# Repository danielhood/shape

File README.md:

# shape
Analog audio shaping toys. Line level moudles as opposed to eurorack i/o, but operating on +12/-12 power rails. The panels are built to be housed in 3U eurorack cases for the power supplies, but use 1/4" audio connectors. 

## 	saturation
A tape saturation/distortion unit based on: http://zadvitsky.com/index.php/studio-devices/tape-saturation-compressor.html
This was built and wired in as a bypassable 2nd stage to the var_state_eq module. A future revision would likely have a blend pot to add in the saturated signal from the EQ'd signal (need to review phase issues).

## var_state_eq
A State Variable Filter 2 Band EQ moudle based on the CALREC PQ1549 (only the HMF and LMF circuits), adapted from: https://www.gyraf.dk/gy_pd/calreq/calrec.htm

## compression
A compressor. WIP. Will be based on a few existing things; other than op-amps, will be discrete components (no THAT chips, etc.).

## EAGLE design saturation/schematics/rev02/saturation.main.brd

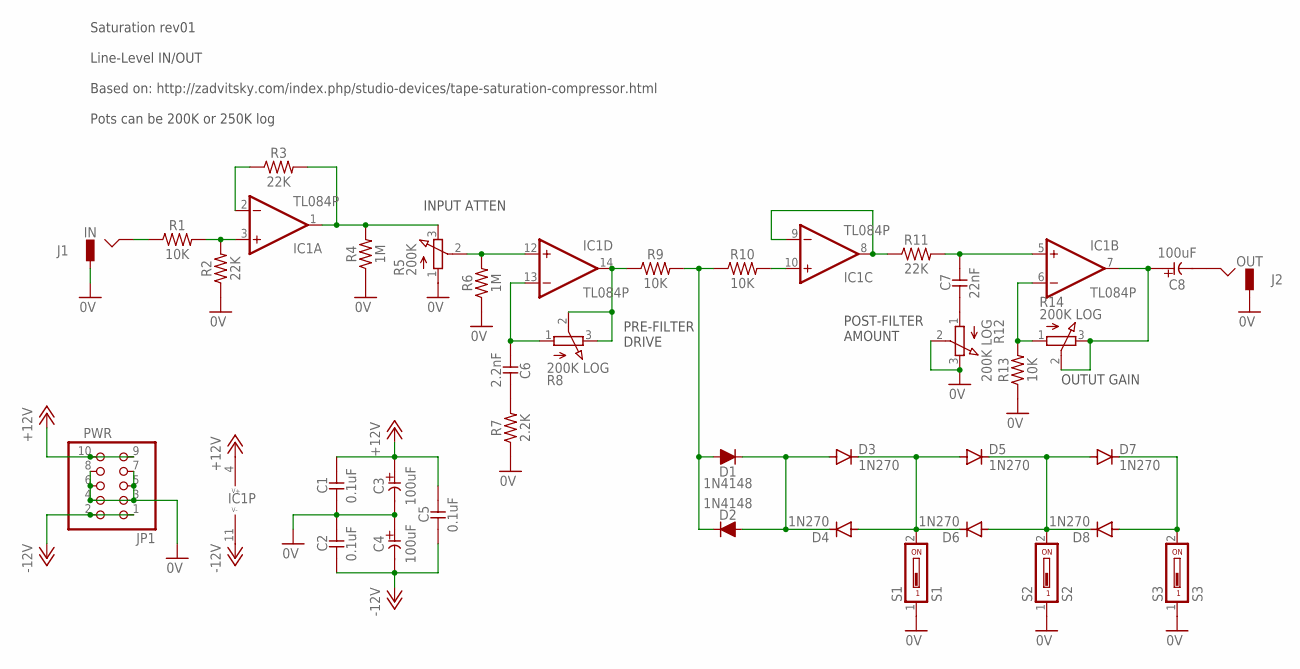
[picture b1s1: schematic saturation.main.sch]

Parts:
C1, C2, C5: 0.1uF; C025-024X044
C3, C4, C8: 100uF; E5-8,5
C6: 2.2nF; C025-024X044
C7: 22nF; C025-024X044
D1, D2: 1N4148; DO34-5
D3, D4, D5, D6, D7, D8: 1N270; DO07
IC1: TL084P; DIL14
J1: IN; JACK-M
J2: OUT; JACK-M
JP1: PWR; 2X05
R1, R9, R10, R13: 10K; 0207/7
R2, R3, R11: 22K; 0207/7
R4, R6: 1M; 0207/7
R5: 200K; 3RP/1610N
R7: 2.2K; 0207/7
R8, R12, R14: 200K LOG; 3RP/1610N
S1: S1; DS-01
S2: S2; DS-01
S3: S3; DS-01

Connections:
0V: C1.2, C2.1, C3.-, C4.+, J1.GND, J2.GND, JP1.3, JP1.4, JP1.5, JP1.6, JP1.7, JP1.8, R2.1, R4.1, R5.1 (A), R6.1, R7.1, R12.2 (S), R12.3 (E), R13.1, S1.1, S2.1, S3.1
+12V: C1.1, C3.+, C5.1, IC1.4 (V+), JP1.9, JP1.10
-12V: C2.2, C4.-, C5.2, IC1.11 (V-), JP1.1, JP1.2
unnamed: D1.A, D2.C, R9.2, R10.1
unnamed: C7.2, R12.1 (A)
unnamed: D1.C, D2.A, D3.A, D4.C
unnamed: D3.C, D4.A, D5.A, D6.C, S1.2
unnamed: IC1.10 (+IN), R10.2
unnamed: D5.C, D6.A, D7.A, D8.C, S2.2
unnamed: IC1.8 (OUT), IC1.9 (-IN), R11.1
unnamed: D7.C, D8.A, S3.2
unnamed: C7.1, IC1.5 (+IN), R11.2
unnamed: IC1.6 (-IN), R13.2, R14.1 (A)
unnamed: C8.+, IC1.7 (OUT), R14.2 (S), R14.3 (E)
unnamed: C8.-, J2.HOT
unnamed: IC1.14 (OUT), R8.2 (S), R8.3 (E), R9.1
unnamed: C6.1, R7.2
unnamed: J1.HOT, R1.1
unnamed: IC1.3 (+IN), R1.2, R2.2
unnamed: IC1.2 (-IN), R3.1
unnamed: IC1.1 (OUT), R3.2, R4.2, R5.3 (E)
unnamed: C6.2, IC1.13 (-IN), R8.1 (A)
unnamed: IC1.12 (+IN), R5.2 (S), R6.2

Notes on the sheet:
Saturation rev01 Line-Level IN/OUT Based on: http://zadvitsky.com/index.php/studio-devices/tape-saturation-compressor.html Pots can be 200K or 250K log
PRE-FILTER DRIVE
POST-FILTER AMOUNT
INPUT ATTEN
OUTUT GAIN

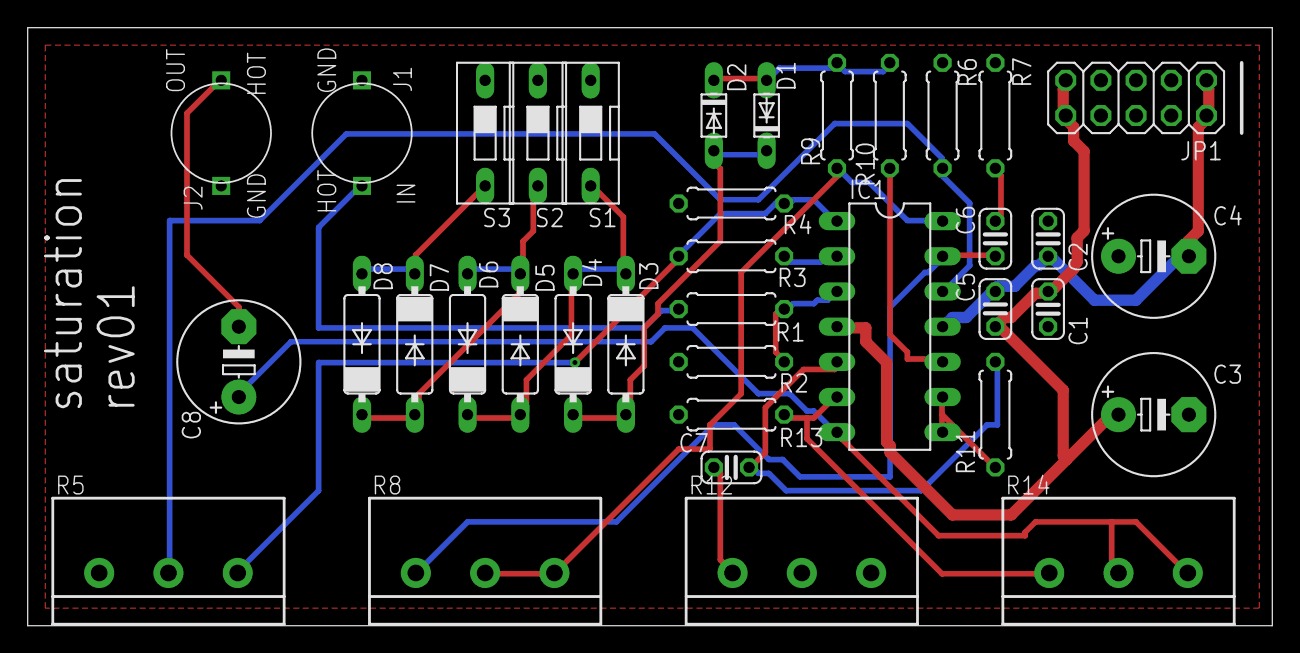
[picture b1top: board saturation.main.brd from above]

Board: 2 copper layers, 89.8 x 43.2 mm, 37 parts (0 on the bottom side), 23 nets.

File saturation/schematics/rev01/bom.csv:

"Qty";"Value";"Device";"Package";"Parts";"Description";"MF";"MPN";"OC_FARNELL";"OC_NEWARK";"POPULARITY";
"3";"0.1uF";"CC-US025-024X044";"C025-024X044";"C1, C2, C5";"CAPACITOR, US symbol";"";"";"";"";"";
"3";"100uF";"CE-USE5-8.5";"E5-8,5";"C3, C4, C8";"ELECTROLYTIC CAPACITOR, US symbol";"";"";"";"";"";
"4";"10K";"R";"0207/7";"R1, R9, R10, R13";"RESISTOR, US symbol";"";"";"";"";"";
"2";"1M";"R";"0207/7";"R4, R6";"RESISTOR, US symbol";"";"";"";"";"";
"6";"1N270";"1N270";"DO07";"D3, D4, D5, D6, D7, D8";"DIODE";"";"";"";"";"0";
"2";"1N4148";"1N4148";"DO34-5";"D1, D2";"DIODE";"";"";"";"";"";
"1";"2.2K";"R";"0207/7";"R7";"RESISTOR, US symbol";"";"";"";"";"";
"1";"2.2nF";"CC-US025-024X044";"C025-024X044";"C6";"CAPACITOR, US symbol";"";"";"";"";"";
"4";"200K";"3RP/1610N";"3RP/1610N";"R5, R8, R12, R14";"Generic single level pcb pot.";"";"";"";"";"8";
"3";"22K";"R";"0207/7";"R2, R3, R11";"RESISTOR, US symbol";"";"";"";"";"";
"1";"22nF";"CC-US025-024X044";"C025-024X044";"C7";"CAPACITOR, US symbol";"";"";"";"";"";
"1";"IN";"JACK-M";"JACK-M";"J1";"";"";"";"";"";"";
"1";"OUT";"JACK-M";"JACK-M";"J2";"";"";"";"";"";"";
"1";"PWR";"PINHD-2X5";"2X05";"JP1";"PIN HEADER";"";"";"";"";"35";
"1";"S1";"DS01";"DS-01";"S1";"DIL/CODE SWITCH";"";"";"unknown";"unknown";"";
"1";"S2";"DS01";"DS-01";"S2";"DIL/CODE SWITCH";"";"";"unknown";"unknown";"";
"1";"S3";"DS01";"DS-01";"S3";"DIL/CODE SWITCH";"";"";"unknown";"unknown";"";
"1";"TL084P";"TL084P";"DIL14";"IC1";"OP AMP";"";"";"";"";"";

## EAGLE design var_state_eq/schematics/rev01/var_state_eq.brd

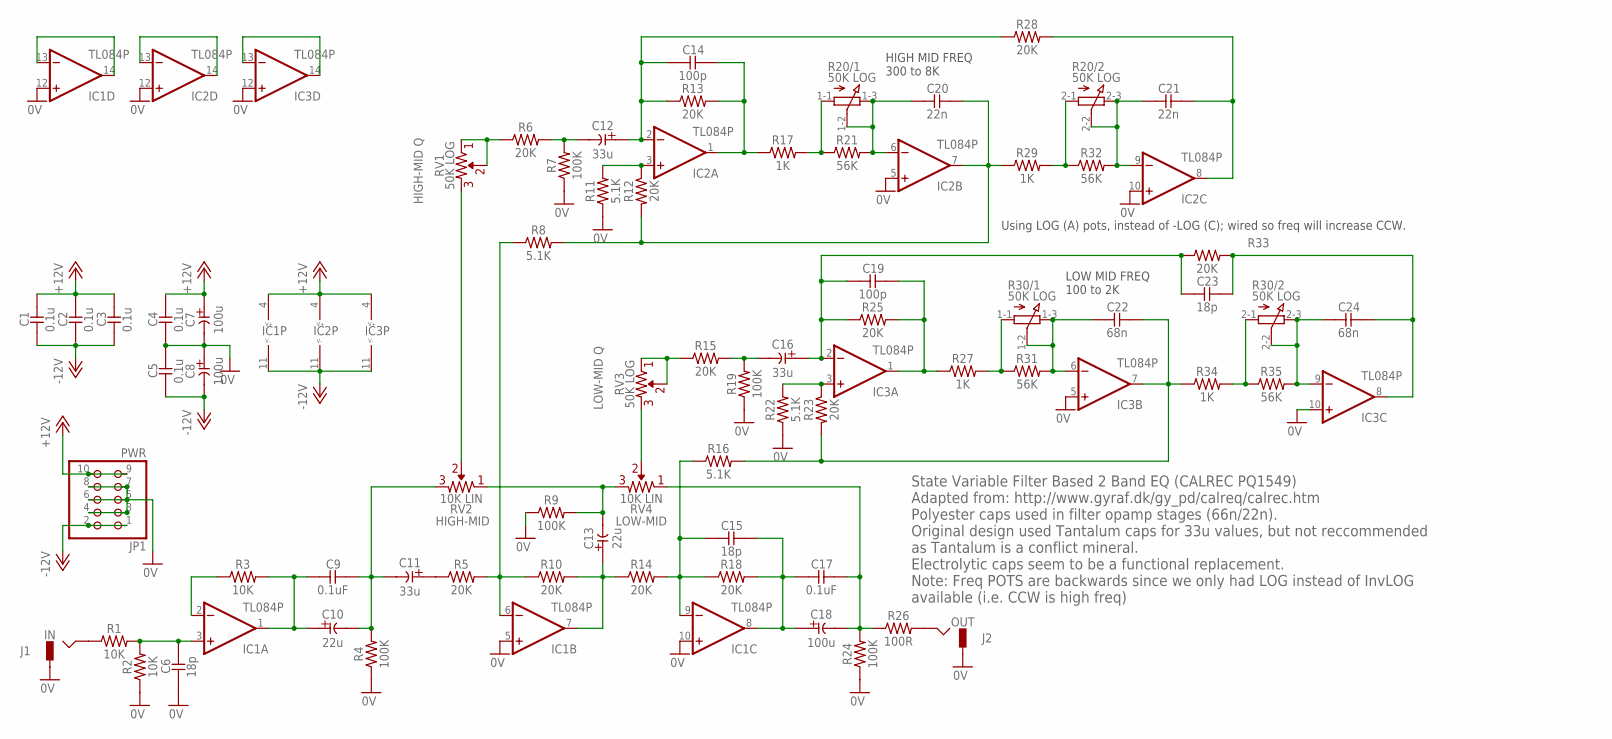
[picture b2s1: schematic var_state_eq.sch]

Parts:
C1, C2, C3, C4, C5: 0.1u; C025-024X044
C6, C15, C23: 18p; C025-024X044
C7, C8, C18: 100u; E5-8,5
C9, C17: 0.1uF; C025-024X044
C10, C13: 22u; E2-5
C11, C12, C16: 33u; E2-5
C14, C19: 100p; C025-024X044
C20, C21: 22n; C050-024X044
C22, C24: 68n; C050-024X044
IC1, IC2, IC3: TL084P; DIL14
J1: IN; JACK-M
J2: OUT; JACK-M
JP1: PWR; 2X05
R1, R2, R3: 10K; 0207/7
R4, R7, R9, R19, R24: 100K; 0207/7
R5, R6, R10, R12, R13, R14, R15, R18, R23, R25, R28, R33: 20K; 0207/7
R8, R11, R16, R22: 5.1K; 0207/7
R17, R27, R29, R34: 1K; 0207/7
R20, R30: 50K LOG; 3RP/1610G
R21, R31, R32, R35: 56K; 0207/7
R26: 100R; 0207/7
RV1, RV3: 50K LOG; R-VAR-PANEL
RV2, RV4: 10K LIN; R-VAR-PANEL

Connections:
0V: C4.2, C5.1, C6.2, C7.-, C8.+, IC1.5 (+IN), IC1.10 (+IN), IC1.12 (+IN), IC2.5 (+IN), IC2.10 (+IN), IC2.12 (+IN), IC3.5 (+IN), IC3.10 (+IN), IC3.12 (+IN), J1.GND, J2.GND, JP1.3, JP1.4, JP1.5, JP1.6, JP1.7, JP1.8, R2.1, R4.1, R7.1, R9.1, R11.1, R19.1, R22.1, R24.1
+12V: C1.1, C2.1, C3.1, C4.1, C7.+, IC1.4 (V+), IC2.4 (V+), IC3.4 (V+), JP1.9, JP1.10
-12V: C1.2, C2.2, C3.2, C5.2, C8.-, IC1.11 (V-), IC2.11 (V-), IC3.11 (V-), JP1.1, JP1.2
unnamed: IC1.13 (-IN), IC1.14 (OUT)
unnamed: IC2.13 (-IN), IC2.14 (OUT)
unnamed: IC3.13 (-IN), IC3.14 (OUT)
unnamed: C11.+, R5.1
unnamed: J1.HOT, R1.1
unnamed: IC1.2 (-IN), R3.1
unnamed: C13.-, R9.2, RV2.R1 (1), RV4.R2 (2)
unnamed: C9.1, C10.-, C11.-, R4.2, RV2.R2 (2)
unnamed: C6.1, IC1.3 (+IN), R1.2, R2.2
unnamed: C13.+, IC1.7 (OUT), R10.2, R14.1
unnamed: C9.2, C10.+, IC1.1 (OUT), R3.2
unnamed: RV1.R2 (2), RV2.VAR
unnamed: IC1.6 (-IN), R5.2, R8.1, R10.1
unnamed: J2.HOT, R26.2
unnamed: C15.2, IC1.9 (-IN), R14.2, R16.1, R18.1
unnamed: C17.1, C18.-, R24.2, R26.1, RV4.R1 (1)
unnamed: R6.1, RV1.R1 (1), RV1.VAR
unnamed: C15.1, C17.2, C18.+, IC1.8 (OUT), R18.2
unnamed: C12.-, R6.2, R7.2
unnamed: C12.+, C14.2, IC2.2 (-IN), R13.1, R28.1
unnamed: C14.1, IC2.1 (OUT), R13.2, R17.1
unnamed: R17.2, R20.1-1 (A), R21.1
unnamed: C20.2, IC2.6 (-IN), R20.1-2 (S), R20.1-3 (E), R21.2
unnamed: R20.2-1 (A), R29.2, R32.1
unnamed: C20.1, IC2.7 (OUT), R8.2, R12.2, R29.1
unnamed: RV3.R2 (2), RV4.VAR
unnamed: C21.2, IC2.9 (-IN), R20.2-2 (S), R20.2-3 (E), R32.2
unnamed: C21.1, IC2.8 (OUT), R28.2
unnamed: IC3.3 (+IN), R22.2, R23.1
unnamed: R15.1, RV3.R1 (1), RV3.VAR
unnamed: C16.-, R15.2, R19.2
unnamed: C16.+, C19.2, C23.2, IC3.2 (-IN), R25.1, R33.1
unnamed: C22.1, IC3.7 (OUT), R16.2, R23.2, R34.1
unnamed: C19.1, IC3.1 (OUT), R25.2, R27.1
unnamed: R27.2, R30.1-1 (A), R31.1
unnamed: C22.2, IC3.6 (-IN), R30.1-2 (S), R30.1-3 (E), R31.2
unnamed: R30.2-1 (A), R34.2, R35.1
unnamed: C24.2, IC3.9 (-IN), R30.2-2 (S), R30.2-3 (E), R35.2
unnamed: C23.1, C24.1, IC3.8 (OUT), R33.2
unnamed: IC2.3 (+IN), R11.2, R12.1

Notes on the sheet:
State Variable Filter Based 2 Band EQ (CALREC PQ1549) Adapted from: http://www.gyraf.dk/gy_pd/calreq/calrec.htm Polyester caps used in filter opamp stages (66n/22n). Original design used Tantalum caps for 33u values, but not reccommended as Tantalum is a conflict mineral. Electrolytic caps seem to 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
HIGH MID FREQ 300 to 8K
HIGH-MID Q
LOW-MID Q
LOW MID FREQ 100 to 2K
Using LOG (A) pots, instead of -LOG (C); wired so freq will increase CCW.
HIGH-MID
LOW-MID

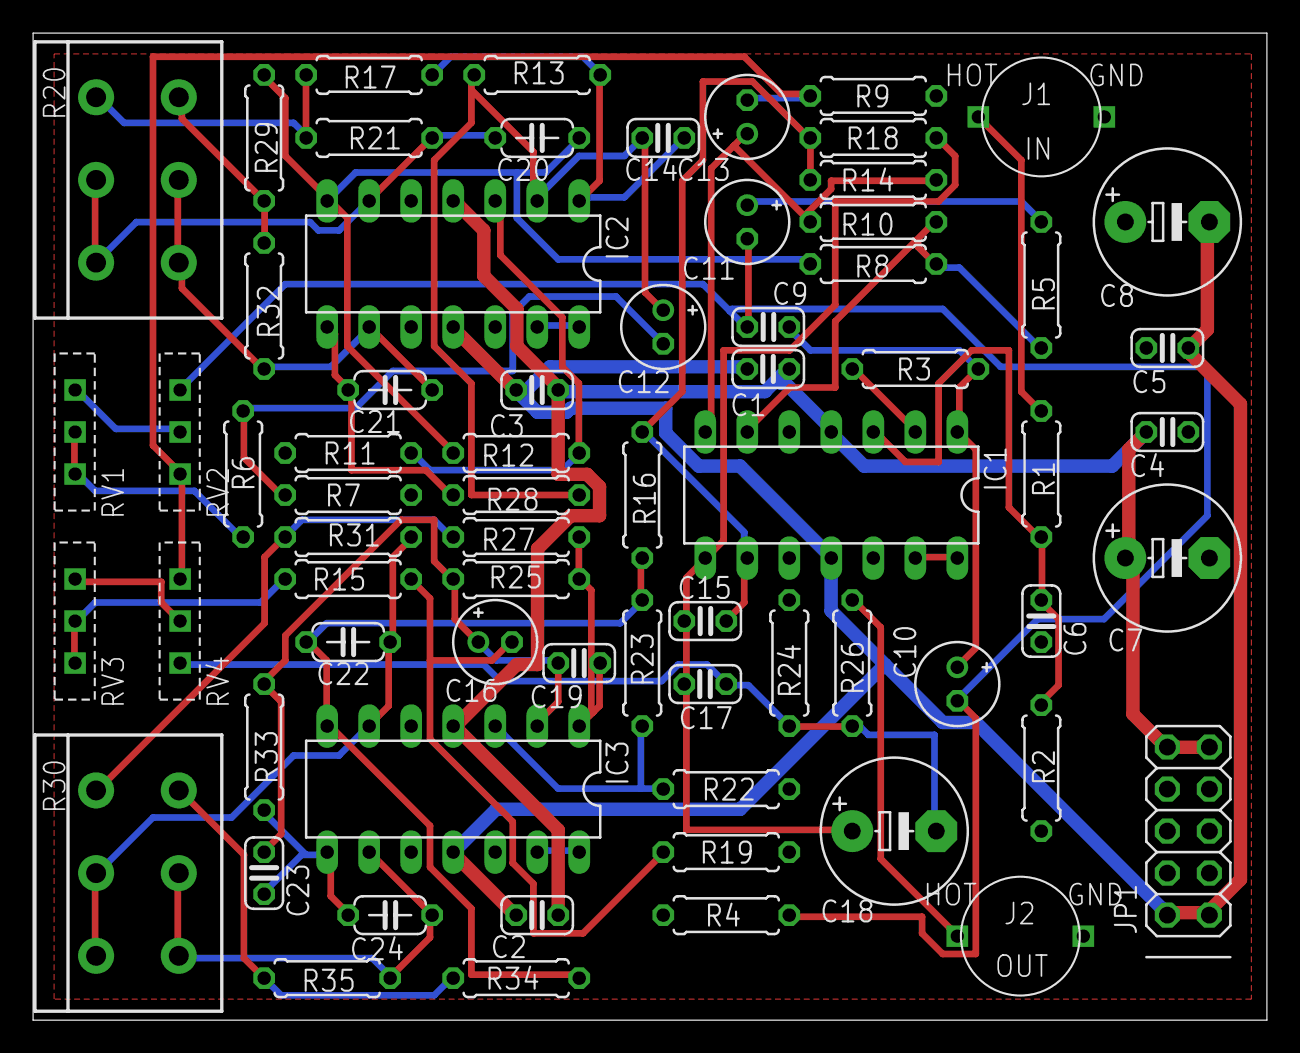
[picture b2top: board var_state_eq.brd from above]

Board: 2 copper layers, 74.6 x 59.7 mm, 69 parts (0 on the bottom side), 43 nets.

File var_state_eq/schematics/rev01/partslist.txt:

Partlist

Exported from var_state_eq.sch at 2020-05-05 8:42 PM

EAGLE Version 9.5.1 Copyright (c) 1988-2019 Autodesk, Inc.

Assembly variant: 

Part     Value          Device           Package      Library  Sheet

C1       0.1u           CC-US025-024X044 C025-024X044 _common  1
C2       0.1u           CC-US025-024X044 C025-024X044 _common  1
C3       0.1u           CC-US025-024X044 C025-024X044 _common  1
C4       0.1u           CC-US025-024X044 C025-024X044 _common  1
C5       0.1u           CC-US025-024X044 C025-024X044 _common  1
C6       18p            CC-US025-024X044 C025-024X044 _common  1
C7       100u           CE-USE5-8.5      E5-8,5       _common  1
C8       100u           CE-USE5-8.5      E5-8,5       _common  1
C9       100n           CC-US025-024X044 C025-024X044 _common  1
C10      22u            CE-USE2-5        E2-5         _common  1
C11      33u            CE-USE2-5        E2-5         _common  1
C12      33u            CE-USE2-5        E2-5         _common  1
C13      22u            CE-USE2-5        E2-5         _common  1
C14      100p           CC-US025-024X044 C025-024X044 _common  1
C15      18p            CC-US025-024X044 C025-024X044 _common  1
C16      33u            CE-USE2-5        E2-5         _common  1
C17      100n           CC-US025-024X044 C025-024X044 _common  1
C18      100u           CE-USE5-8.5      E5-8,5       _common  1
C19      100p           CC-US025-024X044 C025-024X044 _common  1
C20      22n            CC-US050-024X044 C050-024X044 _common  1
C21      22n            CC-US050-024X044 C050-024X044 _common  1
C22      68n            CC-US050-024X044 C050-024X044 _common  1
C23      18p            CC-US025-024X044 C025-024X044 _common  1
C24      68n            CC-US050-024X044 C050-024X044 _common  1
IC1      TL084P         TL084P           DIL14        _common  1
IC2      TL084P         TL084P           DIL14        _common  1
IC3      TL084P         TL084P           DIL14        _common  1
J1       IN             JACK-M           JACK-M       _common  1
J2       OUT            JACK-M           JACK-M       _common  1
JP1      PWR            PINHD-2X5        2X05         pinhead  1
R1       10K            R                0207/7       _common  1
R2       10K            R                0207/7       _common  1
R3       10K            R                0207/7       _common  1
R4       100K           R                0207/7       _common  1
R5       20K            R                0207/7       _common  1
R6       20K            R                0207/7       _common  1
R7       100K           R                0207/7       _common  1
R8       5.1K           R                0207/7       _common  1
R9       100K           R                0207/7       _common  1
R10      20K            R                0207/7       _common  1
R11      5.1K           R                0207/7       _common  1
R12      20K            R                0207/7       _common  1
R13      20K            R                0207/7       _common  1
R14      20K            R                0207/7       _common  1
R15      20K            R                0207/7       _common  1
R16      5.1K           R                0207/7       _common  1
R17      1K             R                0207/7       _common  1
R18      20K            R                0207/7       _common  1
R19      100K           R                0207/7       _common  1
R20      50K LOG        3RP/1610G        3RP/1610G    _common  1
R21      50K            R                0207/7       _common  1
R22      5.1K           R                0207/7       _common  1
R23      20K            R                0207/7       _common  1
R24      100K           R                0207/7       _common  1
R25      20K            R                0207/7       _common  1
R26      22R            R                0207/7       _common  1
R27      1K             R                0207/7       _common  1
R28      20K            R                0207/7       _common  1
R29      1K             R                0207/7       _common  1
R30      50K LOG        3RP/1610G        3RP/1610G    _common  1
R31      50K            R                0207/7       _common  1
R32      50K            R                0207/7       _common  1
R33      20K            R                0207/7       _common  1
R34      1K             R                0207/7       _common  1
R35      50K            R                0207/7       _common  1
RV1      50K LOG        R-VAR-PANEL      R-VAR-PANEL  _common  1
RV2      10K LIN        R-VAR-PANEL      R-VAR-PANEL  _common  1
RV3      50K LOG        R-VAR-PANEL      R-VAR-PANEL  _common  1
RV4      10K LIN        R-VAR-PANEL      R-VAR-PANEL  _common  1

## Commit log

2020-03-19 Initial add of saturation schem and libs
2020-03-19 Inital saturation board layout
2020-03-19 Routing for saturation
2020-03-22 Consolidate power on saturation board
2020-03-22 Saturation schem review
2020-03-23 Inital add for 2 Band EQ
2020-03-24 EQ schem review
2020-05-03 Updated EQ labels
2020-05-03 Updated EQ with as-build values
2020-05-04 Added routed board; switched to film caps
2020-05-06 Updates for part purchase
2020-05-31 Update pot values
2020-05-31 Updated resistor values to 56K
2020-05-31 Updated cap values
2020-06-06 Cam files and packaged gerbers for rev01
2020-06-06 Created rev02
2020-06-06 Flipped sat atten pot
2020-06-13 Added front panel for eq/sat
2023-01-08 Added Compressor POC schem; updated readme
2023-01-08 Updated values from amp build
2023-01-09 Added vca to compressor poc schem
2023-01-11 Updated comp vca values from test build
